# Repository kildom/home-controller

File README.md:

# home-controller

# Najnowsze ustalenia

* Nowy pomysł: Zrobić oddzielny moduł "gateway", zawiera:
  * Step-down 12->5V
  * alt 12V
  * Moduł RS-485
  * Mały mikrokontroler (np. AVR albo STM32C011F4P6) jako gateway między int. UART i RS-485
  * Złącza: GND, in 12V, in alt 12V, out 12V, out 5V, D+, D-, int. UART
  * Dzięki temu znika z tabeli poniżej: RS-485 i alt 12V
  * Gateway może informować local nodes: Output fifo full, voltage: 12V in, out, alt, 5V
* Jednak moduł STM32 zamiast 2 AVRów: [STM32F103C8T6](https://kamami.pl/zestawy-uruchomieniowe-stm32/1192915-kamod-bluepill-plytka-rozwojowa-z-mikrokontrolerem-stm32f103c8t6-kompatybilna-z-weact-bluepill-5906623487998.html)
  * RS-485 (ten wymaga podłączenia do padów 5V-tolerant)
  * Piny podłączone do kwarca mogą być użyte, ale powinny mieć jednakowy stan, więc są traktowane razem jako jedno wyjście - połączone na płytce.
* Gotowe moduły step-down i RS-485 (ten wymaga podłączenia do padów 5V-tolerant)
* Kabel między-modułowy wymaga 2 przewodów: UART i 5V (opcjonalnie GND)
  * Albo może: zrezygnować z 2 IO na rzecz połączeń między-modułowych (wtedy też można usunąć `Shared RS-485+IO` z poniższej tabeli).
* Zaciski IO mogą być w jednym kawałku: https://mou.sr/4oknD5P
* Tabela z zasobami:

|                        | szt. | zaciski 230V | zaciski 12V | Pin µC    | zaciski 230V | zaciski 12V | Pin µC |
| ---------------------- | ---- | ------------ | ----------- | --------- | ------------ | ----------- | ------ |
| Common 230V            | 1    | 1            |             |           | 1            | 0           | 0      |
| Relays 230V common     | 9    | 1            |             | 1         | 9            | 0           | 9      |
| Relays 230V individual | 1    | 2            |             | 1         | 2            | 0           | 1      |
| Relays 12V             | 1    |              | 2           | 1         | 0            | 2           | 1      |
| RS-485                 | 1    |              |             | 3         | 0            | 0           | 3      |
| LED \*                 | 2    |              | 2           | 2         | 0            | 4           | 4      |
| OC                     | 2    |              | 1           | 1         | 0            | 2           | 2      |
| IO                     | 12   |              | 1           | 1         | 0            | 12          | 12     |
| int. UART              | 1    |              |             | 2         | 0            | 0           | 2      |
| GND                    | 1    |              | 2           |           | 0            | 2           | 0      |
| 12V                    | 1    |              | 1           |           | 0            | 1           | 0      |
| alt 12V                | 1    |              | 1           |           | 0            | 1           | 0      |
| Shared RS-485+OC       | 1    |              |             | \-1       | 0            | 0           | \-1    |
| Shared RS-485+IO       | 2    |              |             | \-1       | 0            | 0           | \-2    |
|                        |      |              |             | **RAZEM** | **12**       | **24**      | **31** |
|                        |      |              |             | MAX       | 12           | 24          | 31     |
|                        |      |              |             | Pozostało | 0            | 0           | 0      |

# Inne

* Obudowa: [Kradex ZD1004J](https://botland.com.pl/obudowy/24954-obudowa-modulowa-kradex-zd1004j-abs-v0-na-szyne-din-652x898x716mm-jasnoszara-5905275033614.html)
* Przekaźniki: FORWARD INDUSTRIAL FRM18A-5
* Zaciski 230V: AK3001/6-KD-5.0/KIES
* Zaciski IO/12V: Phoenix Contact PTSA 0,5/ 8-2,5-Z 1990067
* Zabezpieczenie ESD: Littelfuse SP720
* Mikrokontroller: 2x AVR64DD28-I/SO
* Pojedynczy moduł:
  * 11 przekaźników:
    * 9x wspólny zmostkowany styk
    * 1x niezależny z dwoma stykami
    * 1x podłączony do strony styków IO/12V
  * 12 styków 230V
  * 22 styki IO/12V: 8 + 8 + 6
    * 2x2x LED driver
    * 2x Open-Collector
    * 14x IO
    * 1x2x Relay
  * 2x Złącze między modułami (żeby można było łączyć szeregowo):
    * Łączone przez złącze żeńskie kątowe na płytkach po bokach i kołki między modułami (bez kabla), np. [SL 22 164 10 G](https://www.tme.eu/pl/details/sl22.164.10.g)
      * Moduł wykonawczy i moduł zasilający mogą mieć płytki na różnych wysokościach (ok 1.4mm mod. zasilający jest wyżej), więc może trzeba obniżyć jedną, podnieś drugą, lutować złącza inaczej, albo wszystkiego po trochu.
    * 3x Masa
    * 5V
    * 2x 12V
    * UART
    * RS-485 rxd
    * RS-485 txd
    * RS-485 DE
      * W module zasilającym jest pull-down
      * W drugim zączu jest pull-up
      * W ten sposób kontroller będzie rozróżniał, czy został podłączony do moduły zasilającego i jest przekaźnikiem, czy też został podłączony do innego modułu i jest końcowym urządzeniem.
    * **Inna opcja**:
      * Użyć kabla z wieloma złączkami (jak stary kabel IDE)
      * Każdy moduł ma jedno złącze
      * Przewody RS-485 idą innym kablem (między modułowy będzie mieć wtedy 6 pinów, a RS-485 ma 4)
* Moduł zasilający
  * Stabilizator 12V->5V
  * Driver RS-485
  * Wiele wejść 12V: 1 podstawowe, 1 awaryjne
  * 1x Złącze między modułami
  * Zaciski:
    * 2x Masa
    * 2x 12V
    * 2x RS-485
  * Może zmieści się do:
    * Obudowa: [Kradex Z103J 88x34x62mm](https://botland.com.pl/obudowy/10131-obudowa-modulowa-kradex-z103j-88x34x62mm-na-szyne-din-jasna-5905275012343.html),
    * Zaciski: [TBJ05-03-1-G-G](https://www.tme.eu/pl/details/tbj05-03-1-g-g) (albo podobne na 6 torów)
    * Wszystkie zaciski powinny być z jednej strony (od strony niskiego napięcia)
  * **INNA OPCJA**
    * Dodać złącza na płytce dla gotowych układłów step-down i RS-485 i pozbyć się modułu zasilającego, np:
    * https://botland.com.pl/przetwornice-step-down/1349-d24v6f5-przetwornica-step-down-5v-06a-pololu-2107-5904422372132.html
    * https://kamami.pl/konwertery-rs485/574850-modttl-rs485-modul-konwertera-uart-rs-485-5906623456826.html

# Stare informacje

Sprzęt:
* Do skrzynek: NUCLEO-F446ZE https://kamami.pl/stm-nucleo-144/560902-nucleo-f446ze-plytka-rozwojowa-z-mikrokontrolerem-stm32f446zet6-5906623410026.html
* Do skrzynki komunikacyjnej: NUCLEO-F439ZI https://kamami.pl/stm-nucleo-144/572182-nucleo-f439zi-plytka-rozwojowa-z-mikrokontrolerem-stm32f439zit6-5906623410378.html
* Ochrona IO: SP720

Funkcjonalność:
* Napięcie zasilania: 12V, przekażniki, sterowanie diodami
* Napięcie mikrokontrolera: 3.3V
* Kilka wejść zasilania: jedno głowne (z dwiema diodami równolegle z niskim spadkiem), 3-4 dodatkowe z dwiema diodami szeregowo
* Zasilanie 230V jedno przy UPSie z przełączaniem na zasilanie awaryjne
* Wykrywanie jaki tryb zasilania jest aktualnie: normalny czy z UPSa
* Bezpiecznik w kaźdej skrzynce i jedna róźnicówka przy UPSie
* Komunikacja między kontrolerami przez powolny UART na RS-485
* Komunikacja ze światem zewnętrznym przez Ethernet i BLE
* Wyjścia przekażnikowe 230V (tylko NO wystarczą), dużo: lampy (też awaryjne), i rolety (2x na jedną roletę)
* Wyjścia LED, sterowanie prądem - wyjście PWM ze sprzęźeniem zwrotnym na ADC, wyrównanie napięcia przez R i C (PNP, NPN, 4 rezystory i kondensator)
* Wejścia-wyjścia niskonapięciowe 3.3V z SP720, kondensatorem i rezystorem
* Wejścia-wyjścia niskonapięciowe są do: przełączniki, komunikacja, i.t.p.
* Flashowanie za pośrednistwem Ethernet/BLE i rozsyłane dalej do kolenych płytek, jeżeli potrzeba

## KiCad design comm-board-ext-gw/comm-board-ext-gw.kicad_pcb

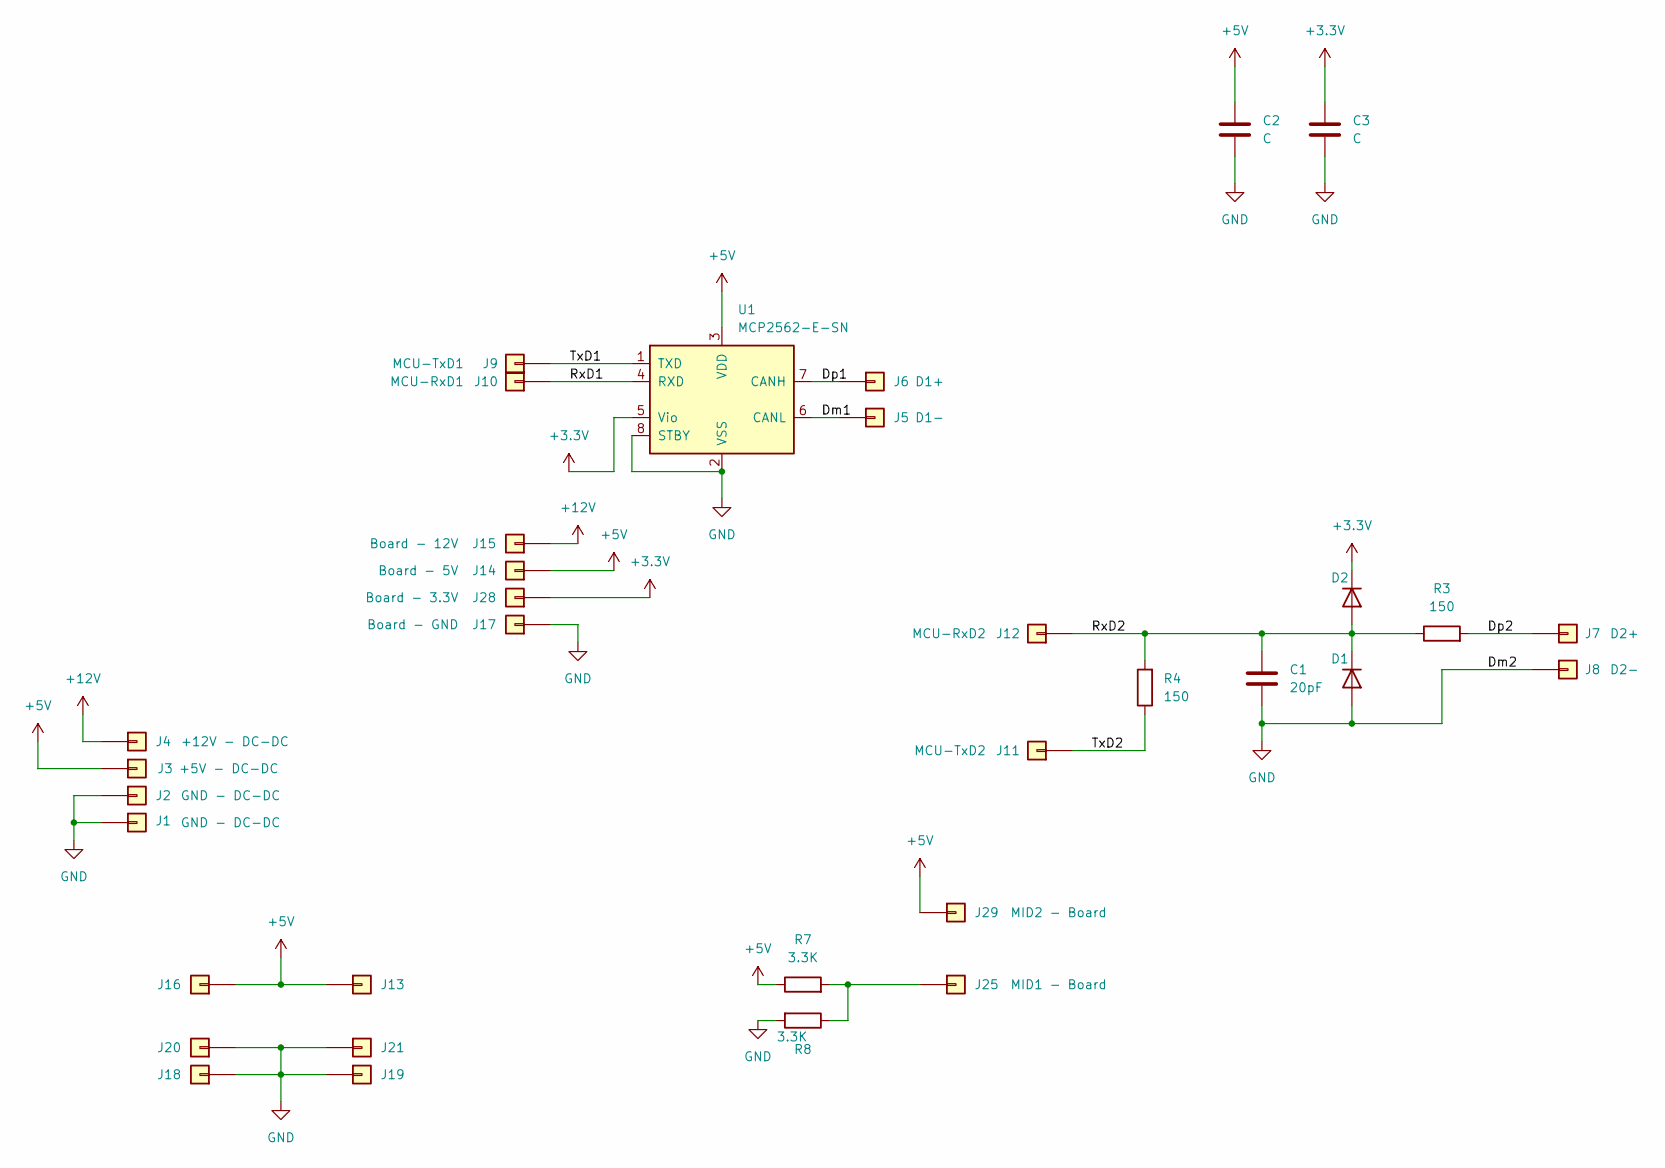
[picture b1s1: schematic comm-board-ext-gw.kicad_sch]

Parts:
C1: 20pF; CNC-mill-0.7-CAP
C2, C3: C; CNC-mill-0.7-CAP
D1, D2: D; CNC-mill-0.7-RES
J1, J2: GND - DC-DC; CHDR
J3: +5V - DC-DC; CHDR
J4: +12V - DC-DC; CHDR
J5: D1-; CHDR
J6: D1+; CHDR
J7: D2+; CHDR
J8: D2-; CHDR
J9: MCU-TxD1; CHDR
J10: MCU-RxD1; CHDR
J11: MCU-TxD2; CHDR
J12: MCU-RxD2; CHDR
J13, J16, J18, J19, J20, J21: CHDR
J14: Board - 5V; CHDR
J15: Board - 12V; CHDR
J17: Board - GND; CHDR
J25: MID1 - Board; CHDR
J28: Board - 3.3V; CHDR
J29: MID2 - Board; CHDR
R3, R4: 150; CNC-mill-0.7-RES
R7, R8: 3.3K; CNC-mill-0.7-RES
U1: MCP2562-E-SN; CNC-mill-0.8-DIP-8

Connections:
+3.3V: C3.1, D2.1 (K), J28.1, U1.5 (Vio)
+5V: C2.1, J3.1, J13.1, J14.1, J16.1, J29.1, R7.1, U1.3 (VDD)
+12V: J4.1, J15.1
/Dm1: J5.1, U1.6 (CANL)
/Dp1: J6.1, U1.7 (CANH)
/Dp2: J7.1, R3.2
/RxD1: J10.1, U1.4 (RXD)
/RxD2: C1.1, D1.1 (K), D2.2 (A), J12.1, R3.1, R4.2
/TxD1: J9.1, U1.1 (TXD)
/TxD2: J11.1, R4.1
GND: C1.2, C2.2, C3.2, D1.2 (A), J1.1, J2.1, J8.1, J17.1, J18.1, J19.1, J20.1, J21.1, R8.2, U1.2 (VSS), U1.8 (STBY)
unnamed: J25.1, R7.2, R8.1

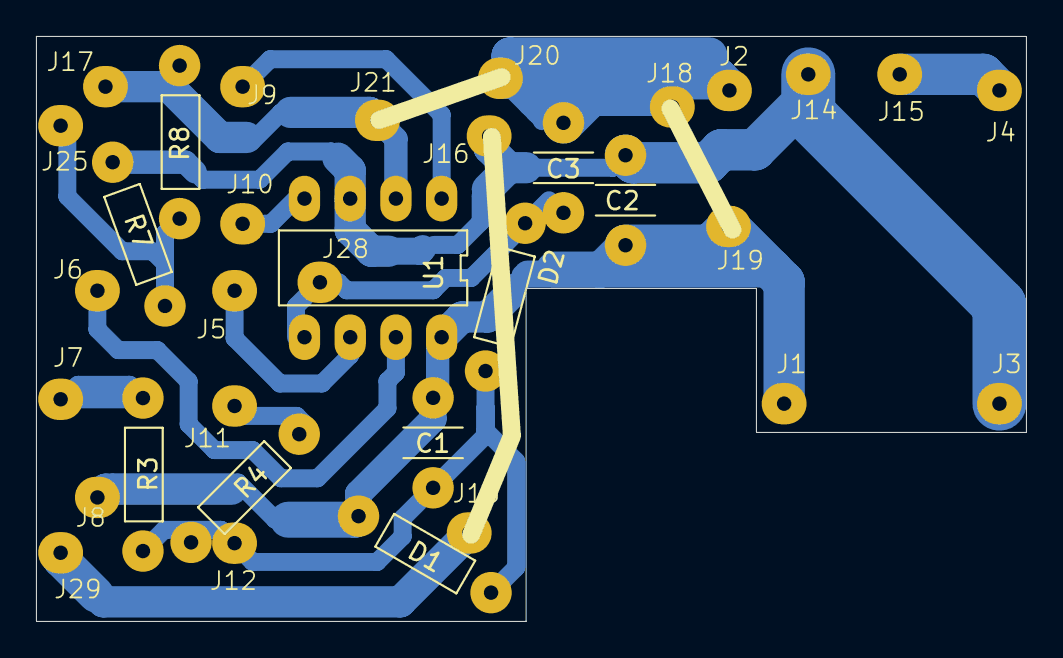
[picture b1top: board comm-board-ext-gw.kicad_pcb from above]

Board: 4 copper layers, 55.0 x 32.5 mm, 34 parts (0 on the bottom side), 12 nets.

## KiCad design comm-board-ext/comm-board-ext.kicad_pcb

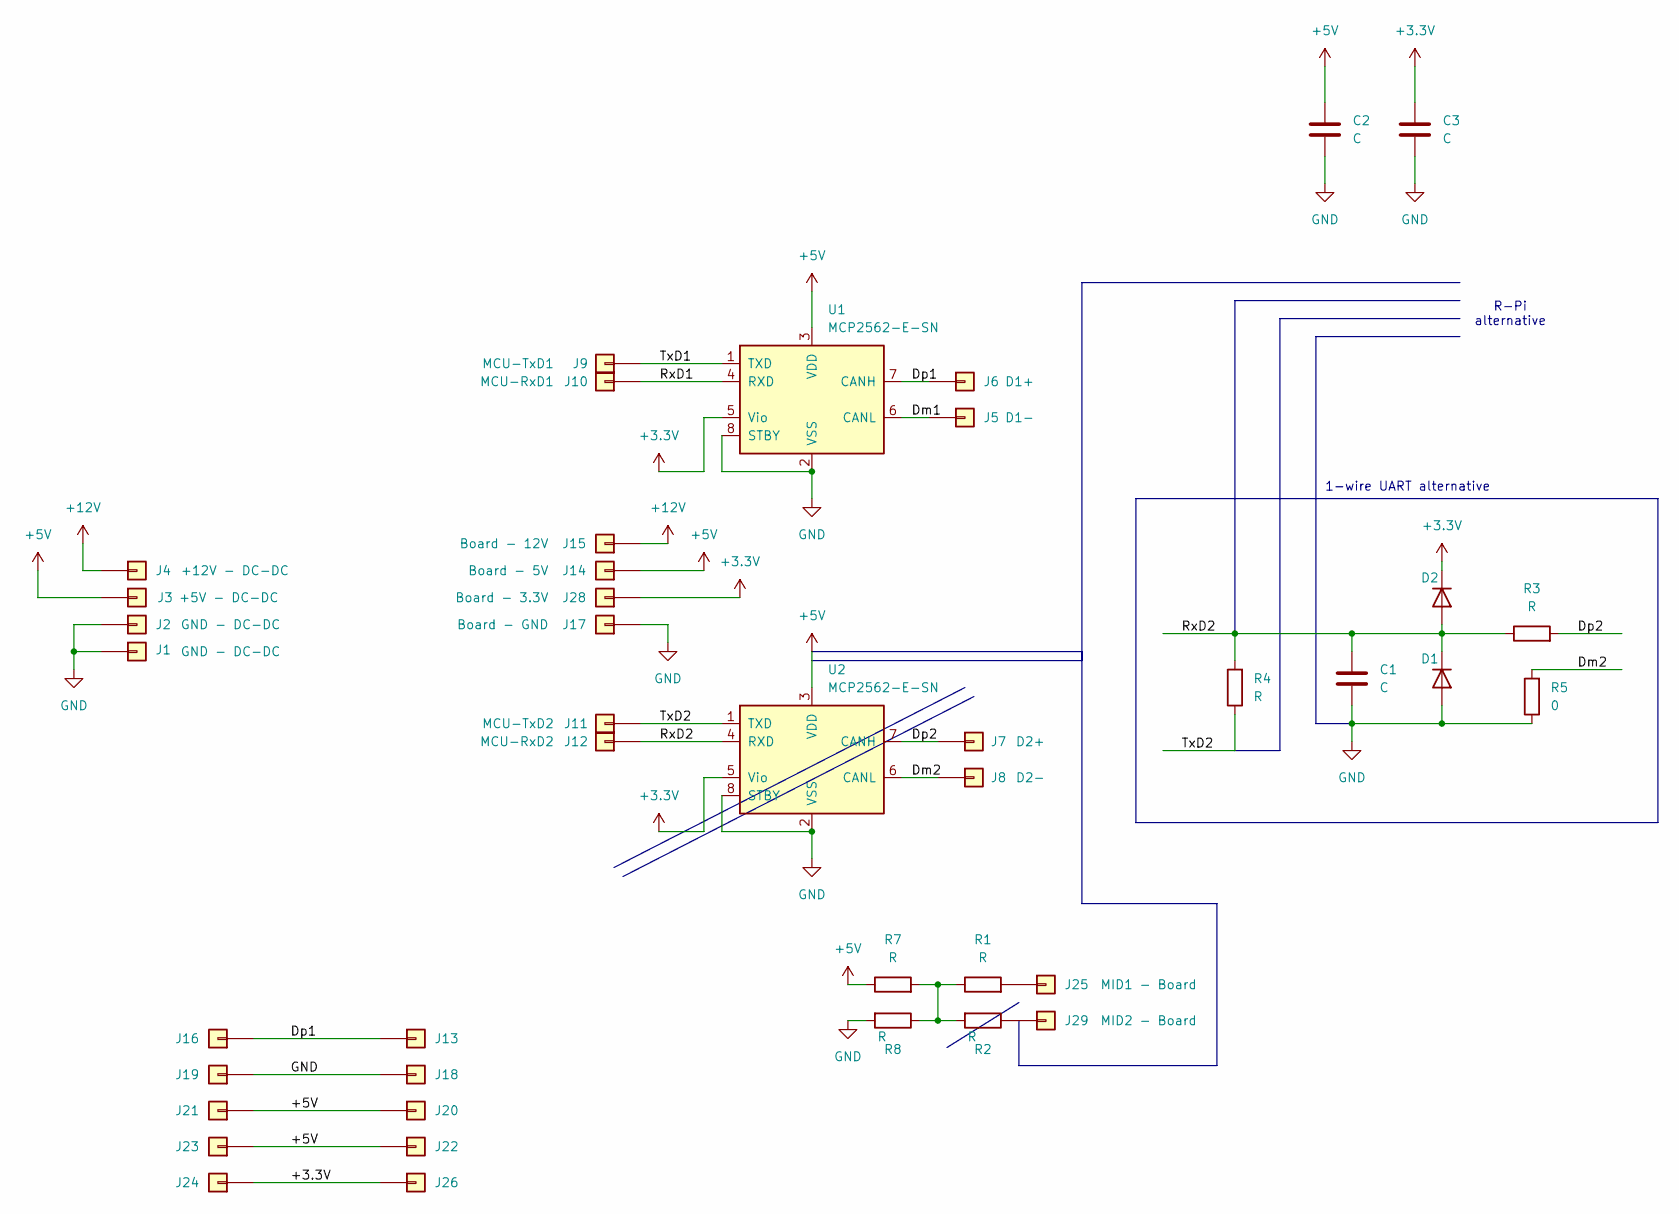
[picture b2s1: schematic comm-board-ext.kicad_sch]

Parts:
C1, C2, C3: C; CNC-mill-0.7-CAP
D1, D2: D; CNC-mill-0.7-RES
J1, J2: GND - DC-DC; CHDR
J3: +5V - DC-DC; CHDR
J4: +12V - DC-DC; CHDR
J5: D1-; CHDR
J6: D1+; CHDR
J7: D2+; CHDR
J8: D2-; CHDR
J9: MCU-TxD1; CHDR
J10: MCU-RxD1; CHDR
J11: MCU-TxD2; CHDR
J12: MCU-RxD2; CHDR
J13, J16, J18, J19, J20, J21, J22, J23, J24, J26: VHDR
J14: Board - 5V; CHDR
J15: Board - 12V; CHDR
J17: Board - GND; CHDR
J25: MID1 - Board; CHDR
J28: Board - 3.3V; CHDR
J29: MID2 - Board; CHDR
R1, R2, R3, R4, R7, R8: R; CNC-mill-0.7-RES
R5: 0; CNC-mill-0.7-RES
U1, U2: MCP2562-E-SN; CNC-mill-0.7-DIP-8

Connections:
+3.3V: C3.1, D2.1 (K), J24.1, J26.1, J28.1, U1.5 (Vio), U2.5 (Vio)
+5V: C2.1, J3.1, J14.1, J20.1, J21.1, J22.1, J23.1, R7.1, U1.3 (VDD), U2.3 (VDD)
+12V: J4.1, J15.1
/Dm1: J5.1, U1.6 (CANL)
/Dm2: J8.1, R5.2, U2.6 (CANL)
/Dp1: J6.1, J13.1, J16.1, U1.7 (CANH)
/Dp2: J7.1, R3.2, U2.7 (CANH)
/RxD1: J10.1, U1.4 (RXD)
/RxD2: C1.1, D1.1 (K), D2.2 (A), J12.1, R3.1, R4.2, U2.4 (RXD)
/TxD1: J9.1, U1.1 (TXD)
/TxD2: J11.1, R4.1, U2.1 (TXD)
GND: C1.2, C2.2, C3.2, D1.2 (A), J1.1, J2.1, J17.1, J18.1, J19.1, R5.1, R8.2, U1.2 (VSS), U1.8 (STBY), U2.2 (VSS), U2.8 (STBY)
unnamed: J25.1, R1.2
unnamed: J29.1, R2.1
unnamed: R1.1, R2.2, R7.2, R8.1

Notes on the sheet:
R-Pi alternative
1-wire UART alternative

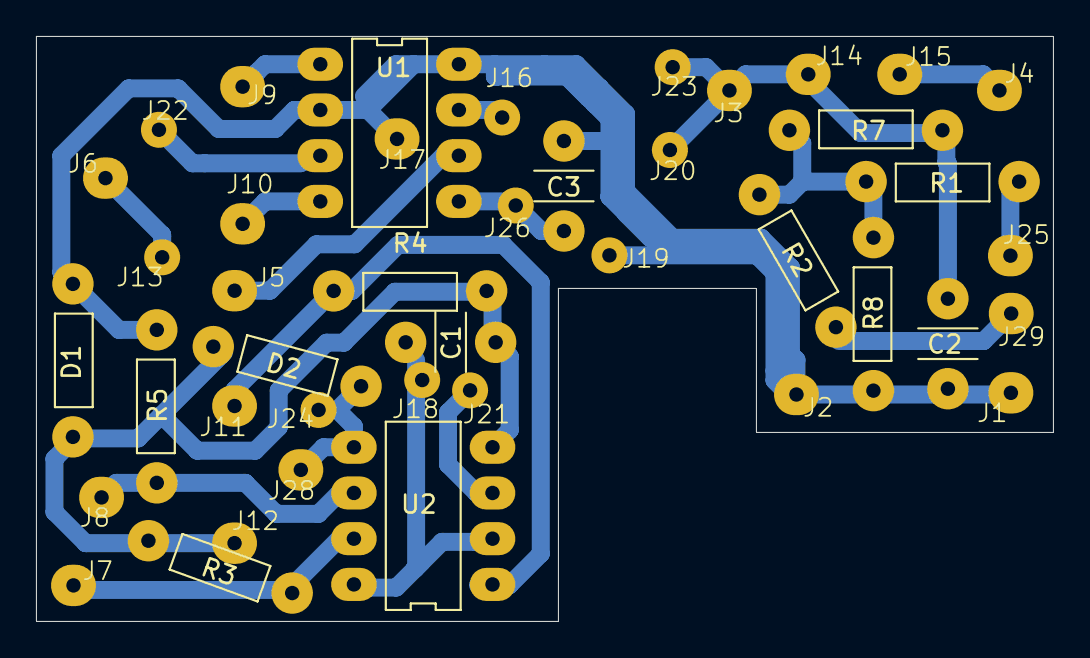
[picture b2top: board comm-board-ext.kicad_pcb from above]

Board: 4 copper layers, 56.5 x 32.5 mm, 42 parts (0 on the bottom side), 15 nets.

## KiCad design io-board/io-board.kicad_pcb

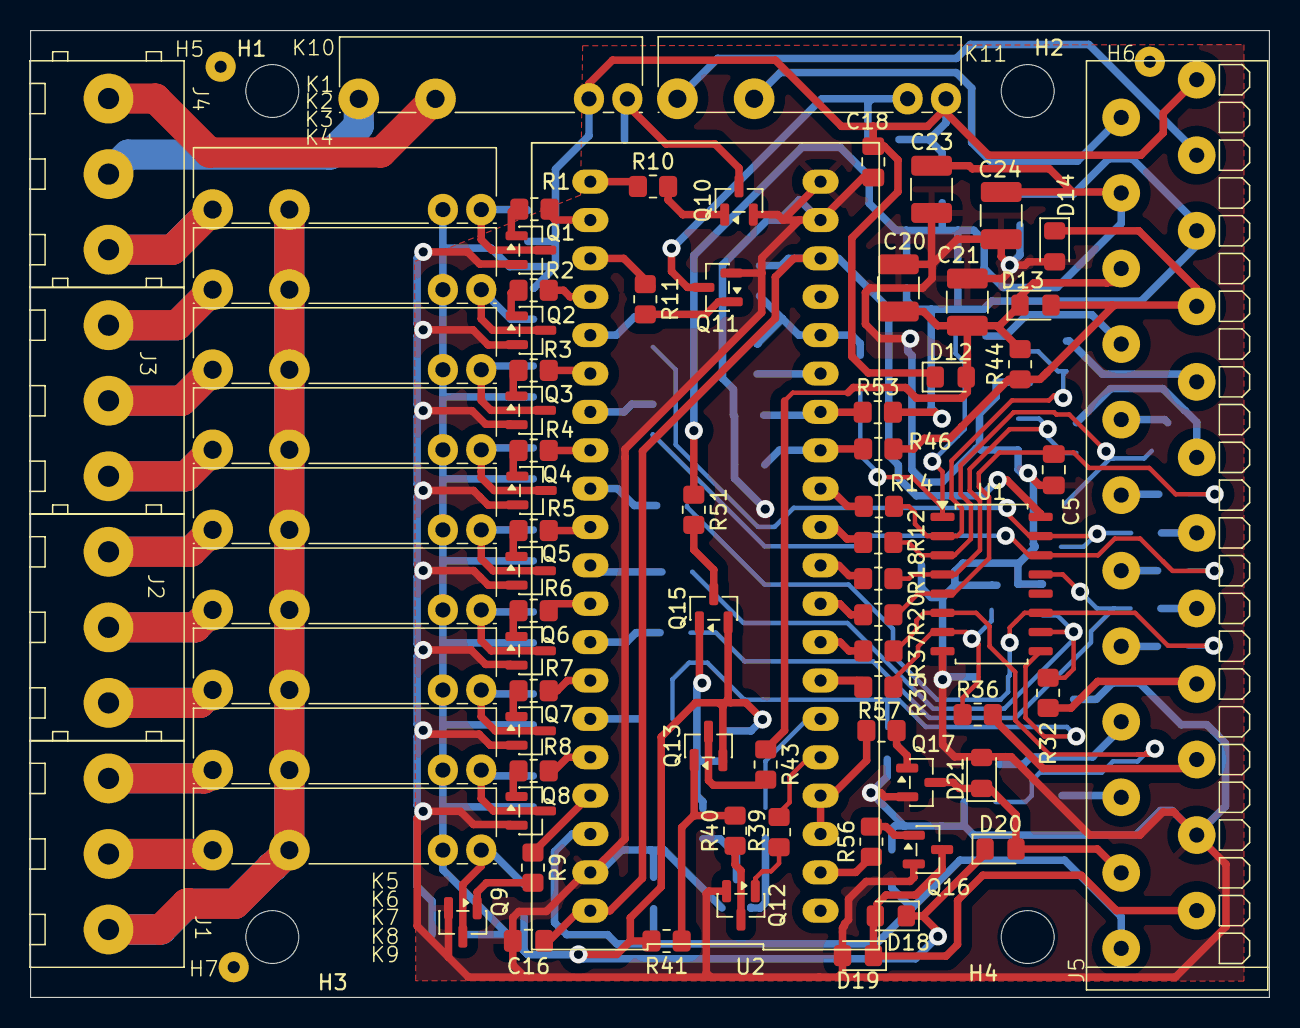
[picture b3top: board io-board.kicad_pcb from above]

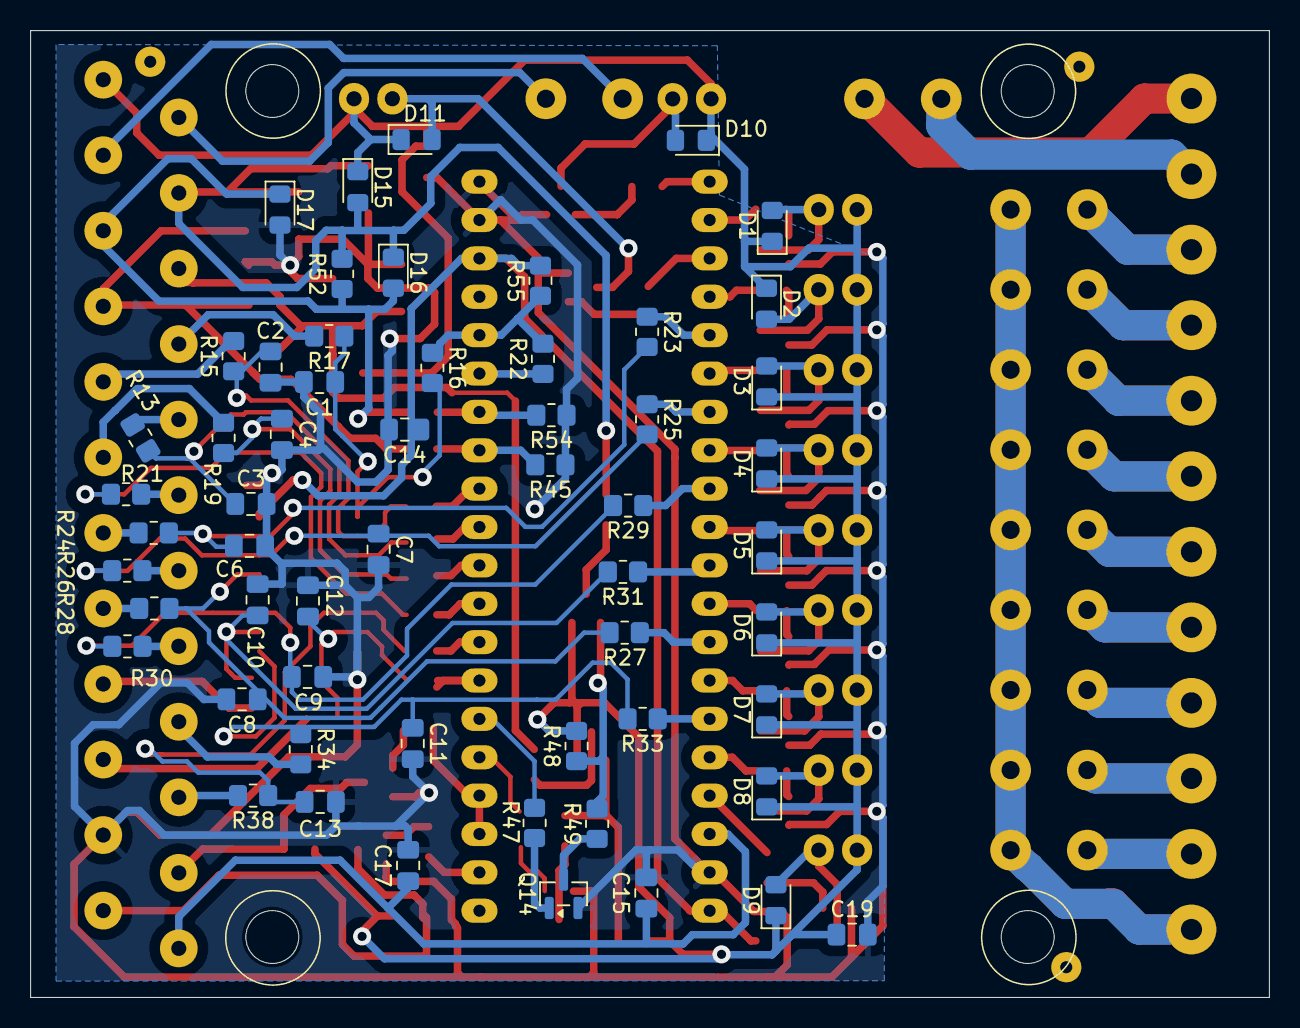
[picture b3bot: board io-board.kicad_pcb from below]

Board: 2 copper layers, 82.0 x 64.0 mm, 141 parts (57 on the bottom side), 113 nets.

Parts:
C1, C2, C3, C4, C5, C6, C7, C8, C9, C10, C11, C12, C13, C14, C15, C16, C17, C18, C19: C; C_0805_2012Metric_Pad1.18x1.45mm_HandSolder
C20, C21, C23, C24: C; C_1210_3225Metric_Pad1.33x2.70mm_HandSolder
D1, D2, D3, D4, D5, D6, D7, D8, D9, D10, D11, D12, D13, D14, D15, D16, D17, D18, D19, D20, D21: D; D_0805_2012Metric_Pad1.15x1.40mm_HandSolder
H1, H2, H3, H4: MountingHole; MountingHole_3.5mm
H5, H6, H7: Conn_01x01; stencil-holder
J1, J2, J3, J4: Conn_01x03; DG128-5.0-03P-14-00A-H
J5: Conn_01x24; PTSA-0.5-24-2.5-Z
K1, K2, K3, K4, K5, K6, K7, K8, K9, K10, K11: FRM18A-5 DC12V; FRM18A-5
Q1, Q2, Q3, Q4, Q5, Q6, Q7, Q8, Q9, Q10, Q11, Q12, Q14, Q16, Q17: NPN; SOT-23
Q13, Q15: PNP; SOT-23
R1, R2, R3, R4, R5, R6, R7, R8, R9, R10, R11, R12, R13, R14, R15, R16, R17, R18, R19, R20, R21, R22, R23, R24, R25, R26, R27, R28, R29, R30, R31, R32, R33, R34, R35, R36, R37, R38, R39, R40, R41, R43, R44, R45, R46, R47, R48, R49, R51, R52, R53, R54, R56, R57: R; R_0805_2012Metric_Pad1.20x1.40mm_HandSolder
R55: 50K; R_0805_2012Metric_Pad1.20x1.40mm_HandSolder
U1: Littelfuse SP720; SOIC-16_4.55x10.3mm_P1.27mm
U2: Kamod BluePill STM32F103C8T6; Kamod-BluePill-STM32F103C8T6

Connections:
+3.3V: C14.1, C16.1, R55.2, U1.16, U2.18, U2.40
+5V: C15.1, C17.1, J5.1, U2.38
+12V: C18.1, C19.1, D1.1 (K), D2.1 (K), D3.1 (K), D4.1 (K), D5.1 (K), D6.1 (K), D7.1 (K), D8.1 (K), D9.1 (K), D10.1 (K), D11.1 (K), D12.1 (K), D15.1 (K), D18.1 (K), D20.1 (K), J5.24, K1.A2, K2.A2, K3.A2, K4.A2, K5.A2, K6.A2, K7.A2, K8.A2, K9.A2, K10.A2, K11.A1, Q13.2 (E), Q15.2 (E), R41.2, R48.2
/ESD1: C1.1, R16.2, R17.1, U1.1
/ESD2: C2.1, R14.2, R15.1, U1.2
/ESD3: C3.1, R12.2, R13.1, U1.3
/ESD4: C4.1, R18.2, R19.1, U1.4
/ESD5: C5.1, R20.2, R21.1, U1.5
/ESD6: C13.1, R37.2, R38.1, U1.6
/ESD7: C12.1, R35.2, R36.1, U1.7
/ESD8: C11.1, R33.2, R34.1, U1.9
/ESD9: C10.1, R31.2, R32.1, U1.10
/ESD10: C9.1, R29.2, R30.1, U1.11
/ESD12: C8.1, R27.2, R28.1, U1.13
/ESD13: C7.1, R25.2, R26.1, U1.14
/ESD14: C6.1, R23.2, R24.1, U1.15
/IO1: J5.16, R15.2
/IO2: J5.15, R13.2
/IO3: J5.14, R19.2
/IO4: J5.13, R21.2
/IO5: J5.12, R24.2
/IO6: J5.11, R26.2
/IO7: J5.10, R28.2
/IO8: J5.9, R30.2
/IO9: J5.8, R32.2
/IO10: J5.7, R34.2
/IO11: J5.6, R36.2
/IO12: J5.5, R38.2
/IO-IN1: R14.1, U2.12
/IO-IN2: R12.1, U2.11
/IO-IN3: R18.1, U2.10
/IO-IN4: R20.1, U2.9
/IO-IN5: R23.1, U2.25
/IO-IN6: R25.1, U2.27
/IO-IN7: R27.1, U2.33
/IO-IN8: R29.1, U2.29
/IO-IN9: R31.1, U2.31
/IO-IN10: R33.1, U2.35
/IO-IN11: R35.1, U2.7
/IO-IN12: R37.1, U2.8
/LED1-FB: R45.2, R46.1, U2.13
/LED1-M: D13.2 (A), D14.1 (K), J5.18, R44.1, R46.2
/LED1-P: C20.1, C21.1, D12.2 (A), D13.1 (K), J5.19, R43.1, R44.2
/LED1-PWM: R39.1, U2.5
/LED2-FB: R53.1, R54.2, U2.14
/LED2-M: D16.2 (A), D17.1 (K), J5.20, R52.1, R53.2
/LED2-P: C23.1, C24.1, D15.2 (A), D16.1 (K), J5.21, R51.1, R52.2
/LED2-PWM: R47.1, U2.6
/OC1: D18.2 (A), D19.1 (K), J5.2, Q16.3 (C)
/OC1-IN: R56.1, U2.2
/OC2: D20.2 (A), D21.1 (K), J5.3, Q17.3 (C)
/OC2-IN: R57.1, U2.3, U2.4
/Relays/REL1-OUT: J4.3, K1.14
/Relays/REL2-OUT: J3.1, K2.14
/Relays/REL3-OUT: J3.2, K3.14
/Relays/REL4-OUT: J3.3, K4.14
/Relays/REL5-OUT: J2.1, K5.14
/Relays/REL6-OUT: J2.2, K6.14
/Relays/REL7-OUT: J2.3, K7.14
/Relays/REL8-OUT: J1.1, K8.14
/Relays/REL9-OUT: J1.2, K9.14
/Relays/REL10-OUT1: J4.1, K10.13
/Relays/REL10-OUT2: J4.2, K10.14
/Relays/REL-COM: J1.3, K1.13, K2.13, K3.13, K4.13, K5.13, K6.13, K7.13, K8.13, K9.13
/UART: J5.17, R17.2
GND: C1.2, C2.2, C3.2, C4.2, C5.2, C6.2, C7.2, C8.2, C9.2, C10.2, C11.2, C12.2, C13.2, C14.2, C15.2, C16.2, C17.2, C18.2, C19.2, C20.2, C21.2, C23.2, C24.2, D14.2 (A), D17.2 (A), D19.2 (A), D21.2 (A), J5.4, Q1.2 (E), Q2.2 (E), Q3.2 (E), Q4.2 (E), Q5.2 (E), Q6.2 (E), Q7.2 (E), Q8.2 (E), Q9.2 (E), Q10.2 (E), Q11.2 (E), Q12.2 (E), Q14.2 (E), Q16.2 (E), Q17.2 (E), R45.1, R54.1, U1.8, U2.19, U2.20, U2.39
unnamed: D1.2 (A), K1.A1, Q1.3 (C)
unnamed: D2.2 (A), K2.A1, Q2.3 (C)
unnamed: D3.2 (A), K3.A1, Q3.3 (C)
unnamed: D4.2 (A), K4.A1, Q4.3 (C)
unnamed: D5.2 (A), K5.A1, Q5.3 (C)
unnamed: D6.2 (A), K6.A1, Q6.3 (C)
unnamed: D7.2 (A), K7.A1, Q7.3 (C)
unnamed: D8.2 (A), K8.A1, Q8.3 (C)
unnamed: D9.2 (A), K9.A1, Q9.3 (C)
unnamed: D10.2 (A), K10.A1, Q10.3 (C)
unnamed: D11.2 (A), K11.A2, Q11.3 (C)
unnamed: Q1.1 (B), R1.2
unnamed: Q2.1 (B), R2.2
unnamed: Q3.1 (B), R3.2
unnamed: Q4.1 (B), R4.2
unnamed: Q5.1 (B), R5.2
unnamed: Q6.1 (B), R6.2
unnamed: Q7.1 (B), R7.2
unnamed: Q8.1 (B), R8.2
unnamed: Q9.1 (B), R9.2
unnamed: Q10.1 (B), R10.2
unnamed: Q11.1 (B), R11.2
unnamed: Q12.1 (B), R39.2
unnamed: Q12.3 (C), R40.1
unnamed: Q13.1 (B), R40.2, R41.1
unnamed: Q13.3 (C), R43.2
unnamed: Q14.1 (B), R47.2
unnamed: Q14.3 (C), R49.1
unnamed: Q15.1 (B), R48.1, R49.2
unnamed: Q15.3 (C), R51.2
unnamed: Q16.1 (B), R56.2
unnamed: Q17.1 (B), R57.2
REL1-IN: R1.1, U2.22
REL2-IN: R2.1, U2.24
REL3-IN: R3.1, U2.26
REL4-IN: R4.1, U2.28
REL5-IN: R5.1, U2.30
REL6-IN: R6.1, U2.32
REL7-IN: R7.1, U2.34
REL8-IN: R8.1, U2.36
REL9-IN: R9.1, U2.37
REL10-IN: R10.1, U2.21
REL11-IN: R11.1, U2.23
REL11-OUT1: J5.22, K11.14
REL11-OUT2: J5.23, K11.13
RXD: R16.1, R22.2, R55.1, U2.16
TXD: R22.1, U2.15

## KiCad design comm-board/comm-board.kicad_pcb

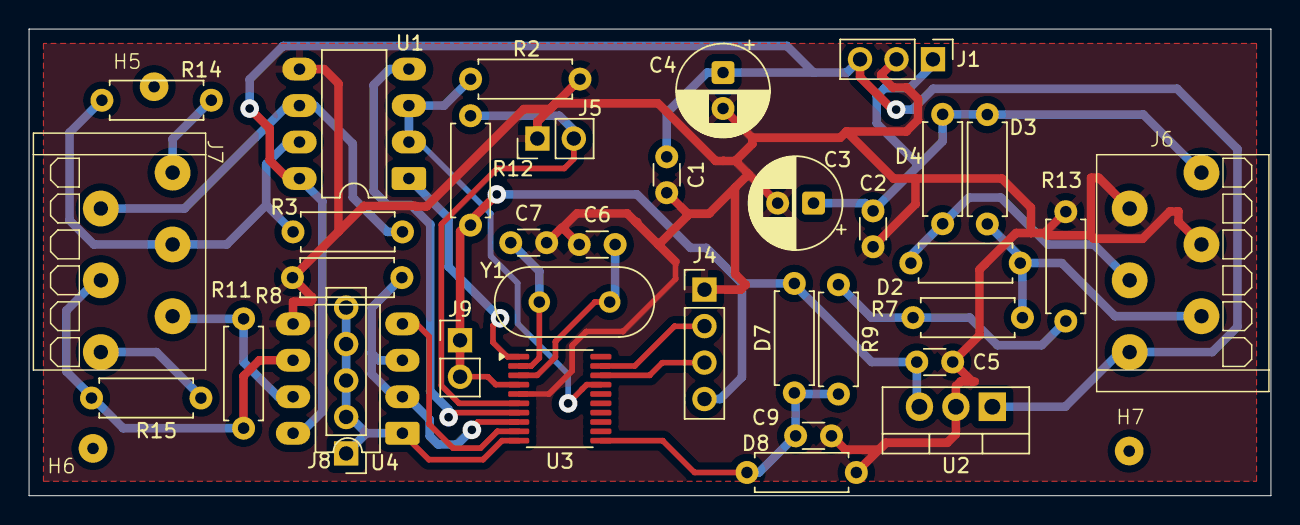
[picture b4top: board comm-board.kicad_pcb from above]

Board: 2 copper layers, 86.5 x 32.5 mm, 38 parts (0 on the bottom side), 25 nets.

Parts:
C1, C2, C5, C6, C7, C9: C_Disc_D3.0mm_W1.6mm_P2.50mm
C3, C4: C_Polarized; CP_Radial_D6.3mm_P2.50mm
D2, D7, D8: D; R_Axial_DIN0207_L6.3mm_D2.5mm_P7.62mm_Horizontal
D3, D4: D_Schottky; R_Axial_DIN0207_L6.3mm_D2.5mm_P7.62mm_Horizontal
H5, H6, H7: Conn_01x01; stencil-holder
J1: Step Down 5V; PinHeader_1x03_P2.54mm_Vertical
J4: ST-LINK; PinHeader_1x04_P2.54mm_Vertical
J5, J9: Conn_01x02; PinHeader_1x02_P2.54mm_Vertical
J6: Power; PTSA-0.5-6-2.5-Z
J7: Communication; PTSA-0.5-6-2.5-Z
J8: PinHeader_1x05_P2.54mm_Vertical
R2, R8: 20K; R_Axial_DIN0207_L6.3mm_D2.5mm_P7.62mm_Horizontal
R3, R11: 50K; R_Axial_DIN0207_L6.3mm_D2.5mm_P7.62mm_Horizontal
R7, R9, R12, R13, R14, R15: 120; R_Axial_DIN0207_L6.3mm_D2.5mm_P7.62mm_Horizontal
U1, U4: MAX485E; DIP-8_W7.62mm_LongPads
U2: LF33_TO220; TO-220-3_Vertical
U3: STM32C011F4Px; TSSOP-20_4.4x6.5mm_P0.65mm
Y1: Crystal; Crystal_HC18-U_Vertical

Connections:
+3.3V: C5.1, D7.1 (K), J4.4, J9.1, J9.2, R12.2, U2.3 (VO), U3.4 (VDD)
+5V: C1.1, C4.1, J1.3, J6.1, U1.8 (VCC), U2.1 (VI), U4.8 (VCC)
+12V: C2.1, C3.1, D3.1 (K), D4.1 (K), J1.1, J6.6
/DE1: R2.1, U1.2 (~RE), U1.3 (DE), U3.17 (PA10/PA12)
/DE2: R8.1, U3.8 (PA1), U4.2 (~RE), U4.3 (DE)
/DI1: U1.4 (DI), U3.7 (PA0)
/DI2: U3.9 (PA2), U4.4 (DI)
/LOCAL+12V: D2.2 (A), D3.2 (A), J6.2, R7.2
/POWER_SENSE: C9.1, D7.2 (A), D8.1 (K), R9.1, U3.11 (PA4)
/REMOTE+12V: D2.1 (K), D4.2 (A), J6.3
/RESET: J5.2, R12.1, U3.6 (PF2)
/RO1: U1.1 (RO), U3.1 (PB7)
/RO2: J8.1, J8.2, J8.3, J8.4, J8.5, U3.10 (PA3), U4.1 (RO)
/RS-485-A1: J7.2, R3.1, U1.6 (A)
/RS-485-A2: J7.4, R11.1, R15.1, U4.6 (A)
/RS-485-B1: J7.3, R3.2, R14.1, U1.7 (B)
/RS-485-B2: J7.5, R11.2, U4.7 (B)
/SWCLK: J4.2, U3.19 (PA14)
/SWDIO: J4.3, U3.18 (PA13)
GND: C1.2, C2.2, C3.2, C4.2, C5.2, C6.2, C7.2, C9.2, D8.2 (A), J1.2, J4.1, J5.1, J6.4, J6.5, R2.2, R8.2, R13.1, U1.5 (GND), U2.2 (GND), U3.5 (VSS), U4.5 (GND)
unnamed: J7.1, R14.2
unnamed: J7.6, R15.2
unnamed: R7.1, R9.2, R13.2
unnamed: C7.1, U3.2 (PC14), Y1.2
unnamed: C6.1, U3.3 (PC15), Y1.1

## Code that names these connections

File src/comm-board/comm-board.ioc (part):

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Mcu.Name=STM32C011F(4-6)Px
Mcu.Package=TSSOP20
Mcu.UserName=STM32C011F6Px
PA1.Signal=GPIO_Input
PA2.GPIOParameters=GPIO_ModeDefaultPP
PA2.GPIO_ModeDefaultPP=GPIO_MODE_AF_PP
PA2.Mode=Asynchronous
PA2.Signal=USART2_TX
PA3.Mode=Asynchronous
PA3.Signal=USART2_RX
PA4.Mode=IN4
PA4.Signal=ADC1_IN4
PC14-OSCX_IN\ (PC14).Mode=HSE-External-Oscillator-REMAPPED
PC14-OSCX_IN\ (PC14).Signal=RCC_OSCX_IN
PC15-OSCX_OUT\ (PC15).Mode=HSE-External-Oscillator-REMAPPED
PC15-OSCX_OUT\ (PC15).Signal=RCC_OSCX_OUT
RCC.HSE_VALUE=20000000
RCC.SYSCLKFreq_VALUE=20000000
RCC.SYSCLKSource=RCC_SYSCLKSOURCE_HSE
board=custom

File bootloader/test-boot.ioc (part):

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Mcu.Name=STM32C011F(4-6)Px
Mcu.Package=TSSOP20
Mcu.UserName=STM32C011F6Px
PA0.GPIOParameters=GPIO_ModeDefaultPP
PA0.GPIO_ModeDefaultPP=GPIO_MODE_AF_OD
PA0.Mode=Asynchronous
PA0.Signal=USART1_TX
PA2.GPIOParameters=GPIO_ModeDefaultPP
PA2.GPIO_ModeDefaultPP=GPIO_MODE_AF_OD
PA2.Mode=Asynchronous
PA2.Signal=USART2_TX
PA3.Mode=Asynchronous
PA3.Signal=USART2_RX
PB7.Mode=Asynchronous
PB7.Signal=USART1_RX
RCC.HSE_VALUE=20000000
RCC.SYSCLKFreq_VALUE=48000000
board=custom

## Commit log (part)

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2025-09-29 Add KiCad board project
2025-09-29 Add STM32 module
2025-09-29 Almost all connected except OC and LED drivers
2025-09-30 All added and connected in PCB. Cleanup needed.
2025-10-01 PCB: All component locations done
2025-10-03 PCB: All in place, need to prepare for production
2025-10-03 PCB: Stencil holders and production configuration
2025-10-03 PCB: Fixups
2025-10-05 PCB: comm-board draft
2025-10-05 PCB: comm: Cleanup and production configuration
2025-10-05 PCB: comm: Add stencil holder
2025-10-26 PCB: comm: Arranged components labels
2025-10-26 PCB: io: Removed unneeded res in LED driver
2025-10-27 Document low-level protocol and packet format
    Added low-level protocol details and packet format specifications.
2025-10-27 Update transmission wait time description in README
2025-10-27 Enhance README with STM32 UART practical approaches
    Added practical approach examples for STM32 UART communication.
2025-10-27 Draft: kodowanie pakietów
2025-11-03 Protocol drafts
2025-11-03 Update protocol description for package handling
2025-11-03 Add SET_NAME functionality for device name change
2025-11-03 Add detailed protocol specifications for network layers
2025-12-30 PCB: comm-board: component values and BOM
2026-01-01 PCB: io-board: component values and BOM
2026-01-02 PCB: small BOM updates
2026-01-11 Remove gtest submodule
2026-01-11 Initial sources and unit tests with coverage
2026-01-11 More unit tests for PacketInQueue
2026-01-17 First drafts of soft for comm-board
2026-01-20 Revise Physical Layer communication methods
    Updated the Physical Layer section with new communication protocols and removed old methods.
2026-01-21 New CAN-based physical layer, application protocol description, hi-res timers drafts.
2026-01-24 Draft of webserver with authentication
2026-01-24 CAN extension PCB for comm-board
2026-01-25 Reduce dependencies of server to allow running on RPiZero
2026-01-26 Draft of react web interface
2026-02-23 comm-board-ext: Modified for CNC milling
2026-03-11 Enhance protocol with new frame structure option
    Added option for frame structure to improve transmission reliability and reduce collision probability.
2026-03-11 Update protocol.md with transmission error handling
    Added note about transmission errors when multiple transmitters are present.
2026-03-11 Clarify frame validation and timing logic
    Updated frame transmission checks and timing calculations.
2026-03-11 Revise byte transmission options and collision handling
    Updated protocol details for byte transmission and collision handling.
2026-03-12 Document Bootloader Protocol in protocol.md
    Added Bootloader Protocol section with detailed specifications.
2026-03-15 Add ESC masking to mask variable in packet.cpp
    Apply ESC masking to the mask variable before processing data.
2026-03-16 comm-board: New "Gateway" and "Router" extensions and removed old "Universal"
2026-03-16 Add bootloader
2026-03-16 Enhance bootloader functionality and configuration
    - Updated CPU clock frequency from 24MHz to 48MHz in project settings.
    - Increased FLASH memory size from 6K to 16K in linker script.
    - Added RNG (Random Number Generator) implementation with functions for generating and adding entropy.
    - Modified main.c to integrate RNG and adjust timing calculations.
    - Revised UART settings and added overrun detection disable feature for USART1 and USART2.
    - Cleaned up project configuration file by removing unnecessary CRC parameters.
2026-03-16 Add bootloader programming functionality and UART communication
    - Implemented programming commands (init, erase, write, read, reset) in prog.c.
    - Defined device information structure for STM32C011xx.
    - Created UART communication functions for data transmission and reception in uart.c.
    - Removed unused RNG functionality by deleting rng.c.
    - Added header file for programming commands and UART interface.
    - Enhanced packet handling with CRC validation and escape sequences for UART communication.
2026-03-16 Refactor UART communication and add support for PortState structure
2026-03-16 Refactor bootloader code and update project settings
    - Updated .cproject and .settings/stm32cubeide.project.prefs to reflect new configurations.
    - Added NUM_PORTS definition to support multiple USART ports in uart.c.
    - Removed cfg.h and prog.c files as they were no longer needed.
    - Refactored uart.c to improve structure and readability, including initialization and command handling.
    - Updated linker script STM32C011F6PX_FLASH.ld to adjust RAM size for magic value.
    - Enhanced uartPoll function to handle multiple USART ports and added packet handling logic.
2026-03-16 Update bootloader configuration and memory settings; adjust heap size and flash memory length
2026-03-16 Add test application and update bootloader configurations
    - Created a new test application with TypeScript and Vite configuration.
    - Updated bootloader launch configurations to disable stopping at main for both Release and Debug modes.
    - Modified the IOC file to set GPIO parameters for PA0 and PA2 to use alternate function open-drain mode.
2026-03-16 Refactor bootloader and test application: update CRC calculation, modify UART output type, and adjust GPIO settings
2026-03-16 Update packet format and mask calculation in protocol documentation
2026-03-21 Moved bootloader source files
2026-03-21 bootloader: Working all build configurations
2026-03-23 Implement Data Link Layer with packet encoding/decoding, CRC32 validation, and serial communication
    - Added DATA_LINK.md documentation for Data Link Layer implementation.
    - Created data_link.py for handling packet encoding, decoding, and CRC32 checks.
    - Introduced addresses.py for managing address allocation and keep-alive functionality.
    - Updated commands.py to include keep_alive and release_addr command handlers.
    - Implemented serial_daemon.py for serial communication with support for sending and receiving data.
    - Enhanced main.py to integrate Data Link Layer and serial daemon, including session management.
2026-03-23 Add security considerations review for password-based authentication and cryptography
